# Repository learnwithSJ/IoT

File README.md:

# Smart AI Plug

An ESP32-S3 based IoT smart plug designed for remote and scheduled control of electrical appliances.

> **Project Status:** PCB Design Completed — Hardware Assembly and Testing Not Yet Performed.

## Overview

Smart AI Plug is a smart plug concept designed around the ESP32-S3 microcontroller. The system is intended to provide wireless appliance control along with scheduled operation.

The complete circuit and PCB were designed using **KiCad**.

## Features

* ESP32-S3 based design
* Single-channel relay control (SPDT)
* Wi-Fi and Bluetooth connectivity
* Relay-based appliance switching
* RTC-based scheduled operation
* USB-C interface
* Onboard RTC with battery backup (DS3231M + CH291-1220LF)
* Status LEDs - Network, Error, General indication
* Buzzer feedback (MLT-8530)
* 4x tactile switches for local control
* AC-DC power supply section
* PCB protection circuitry
* Compact PCB design

## 🏗️ System Architecture

```
220V AC Input
     │
     ▼
[F1 Fuse 500mA] ──→ [MOV RV1 Surge Protection]
     │
     ▼
[HLK-5M05] ──→ 5V DC
     │
     ├──→ [Relay K1 SPDT] ──→ Load Output (Screw Terminal J2)
     │
     └──→ [AMS1117-3.3] ──→ 3.3V DC
               │
               ├──→ [ESP32-S3-WROOM-1] ←→ WiFi / BLE
               ├──→ [DS3231M RTC] (I2C)
               ├──→ [Status LEDs]
               ├──→ [Buzzer MLT-8530]
               ├──→ [Tactile Switches x4]
               └──→ [USB-C] ──→ Firmware Flash / Serial Debug
```

---

## 🔧 Hardware Specifications

| Parameter | Details |
|---|---|
| Microcontroller | ESP32-S3-WROOM-1 |
| Input Voltage | 220V AC |
| Operating Voltage | 5V DC / 3.3V DC |
| Power Supply Module | HLK-5M05 (220VAC → 5VDC) |
| LDO Regulator | AMS1117-3.3 |
| Relay | SPDT — 1 Channel |
| RTC | DS3231M (I2C) |
| RTC Battery | CH291-1220LF (Coin Cell) |
| USB Connector | USB-C (USB 2.0) |
| ESD Protection | USBLC6-2P6 |
| Surge Protection | MOV 10D561K |
| Fuse | 500mA / 250V |
| Status LEDs | Red, Blue, Green |
| Buzzer | MLT-8530 |
| Switches | 4x Tactile + 1x Boot + 1x Reset |
| PCB Tool | KiCad 9.0.1 |
| Board Revision | Rev-v0.1.0A |

---

## PCB Design

The schematic and PCB layout were designed using **KiCad**.

## Repository Structure

```text
KiCad/          → KiCad schematic, PCB and project files
Documentation/  → Design documents and diagrams
Images/         → Project images
BOM/            → Bill of Materials
Firmware/       → Firmware documentation
```

## Project Status

The schematic and PCB layout have been completed in KiCad.

The current version is a **design/prototype-stage project**. Physical PCB fabrication, assembly, firmware deployment, and hardware testing have not yet been completed.

## Future Improvements

* Fabricate and assemble the PCB
* Develop and test ESP32-S3 firmware
* Add cloud-based appliance control
* Integrate voice assistant support
* Perform electrical safety and functional testing
* Optimize PCB size and power consumption

## 🏭 Manufacturing

Fabrication files are located in `Hardware/3-Manufacturing-Files/` and include:

- **Gerber files** - for PCB fabrication
- **BOM (Bill of Materials)** - component list with values and part numbers
- **CPL (Component Placement List)** - for SMT assembly

## Designed By

**Shubhank**

## Acknowledgements

Special thanks to **Ampnics** for creating and sharing the original Zeen AI Plug project and providing the YouTube tutorial and open-source resources that helped me understand and recreate this project.

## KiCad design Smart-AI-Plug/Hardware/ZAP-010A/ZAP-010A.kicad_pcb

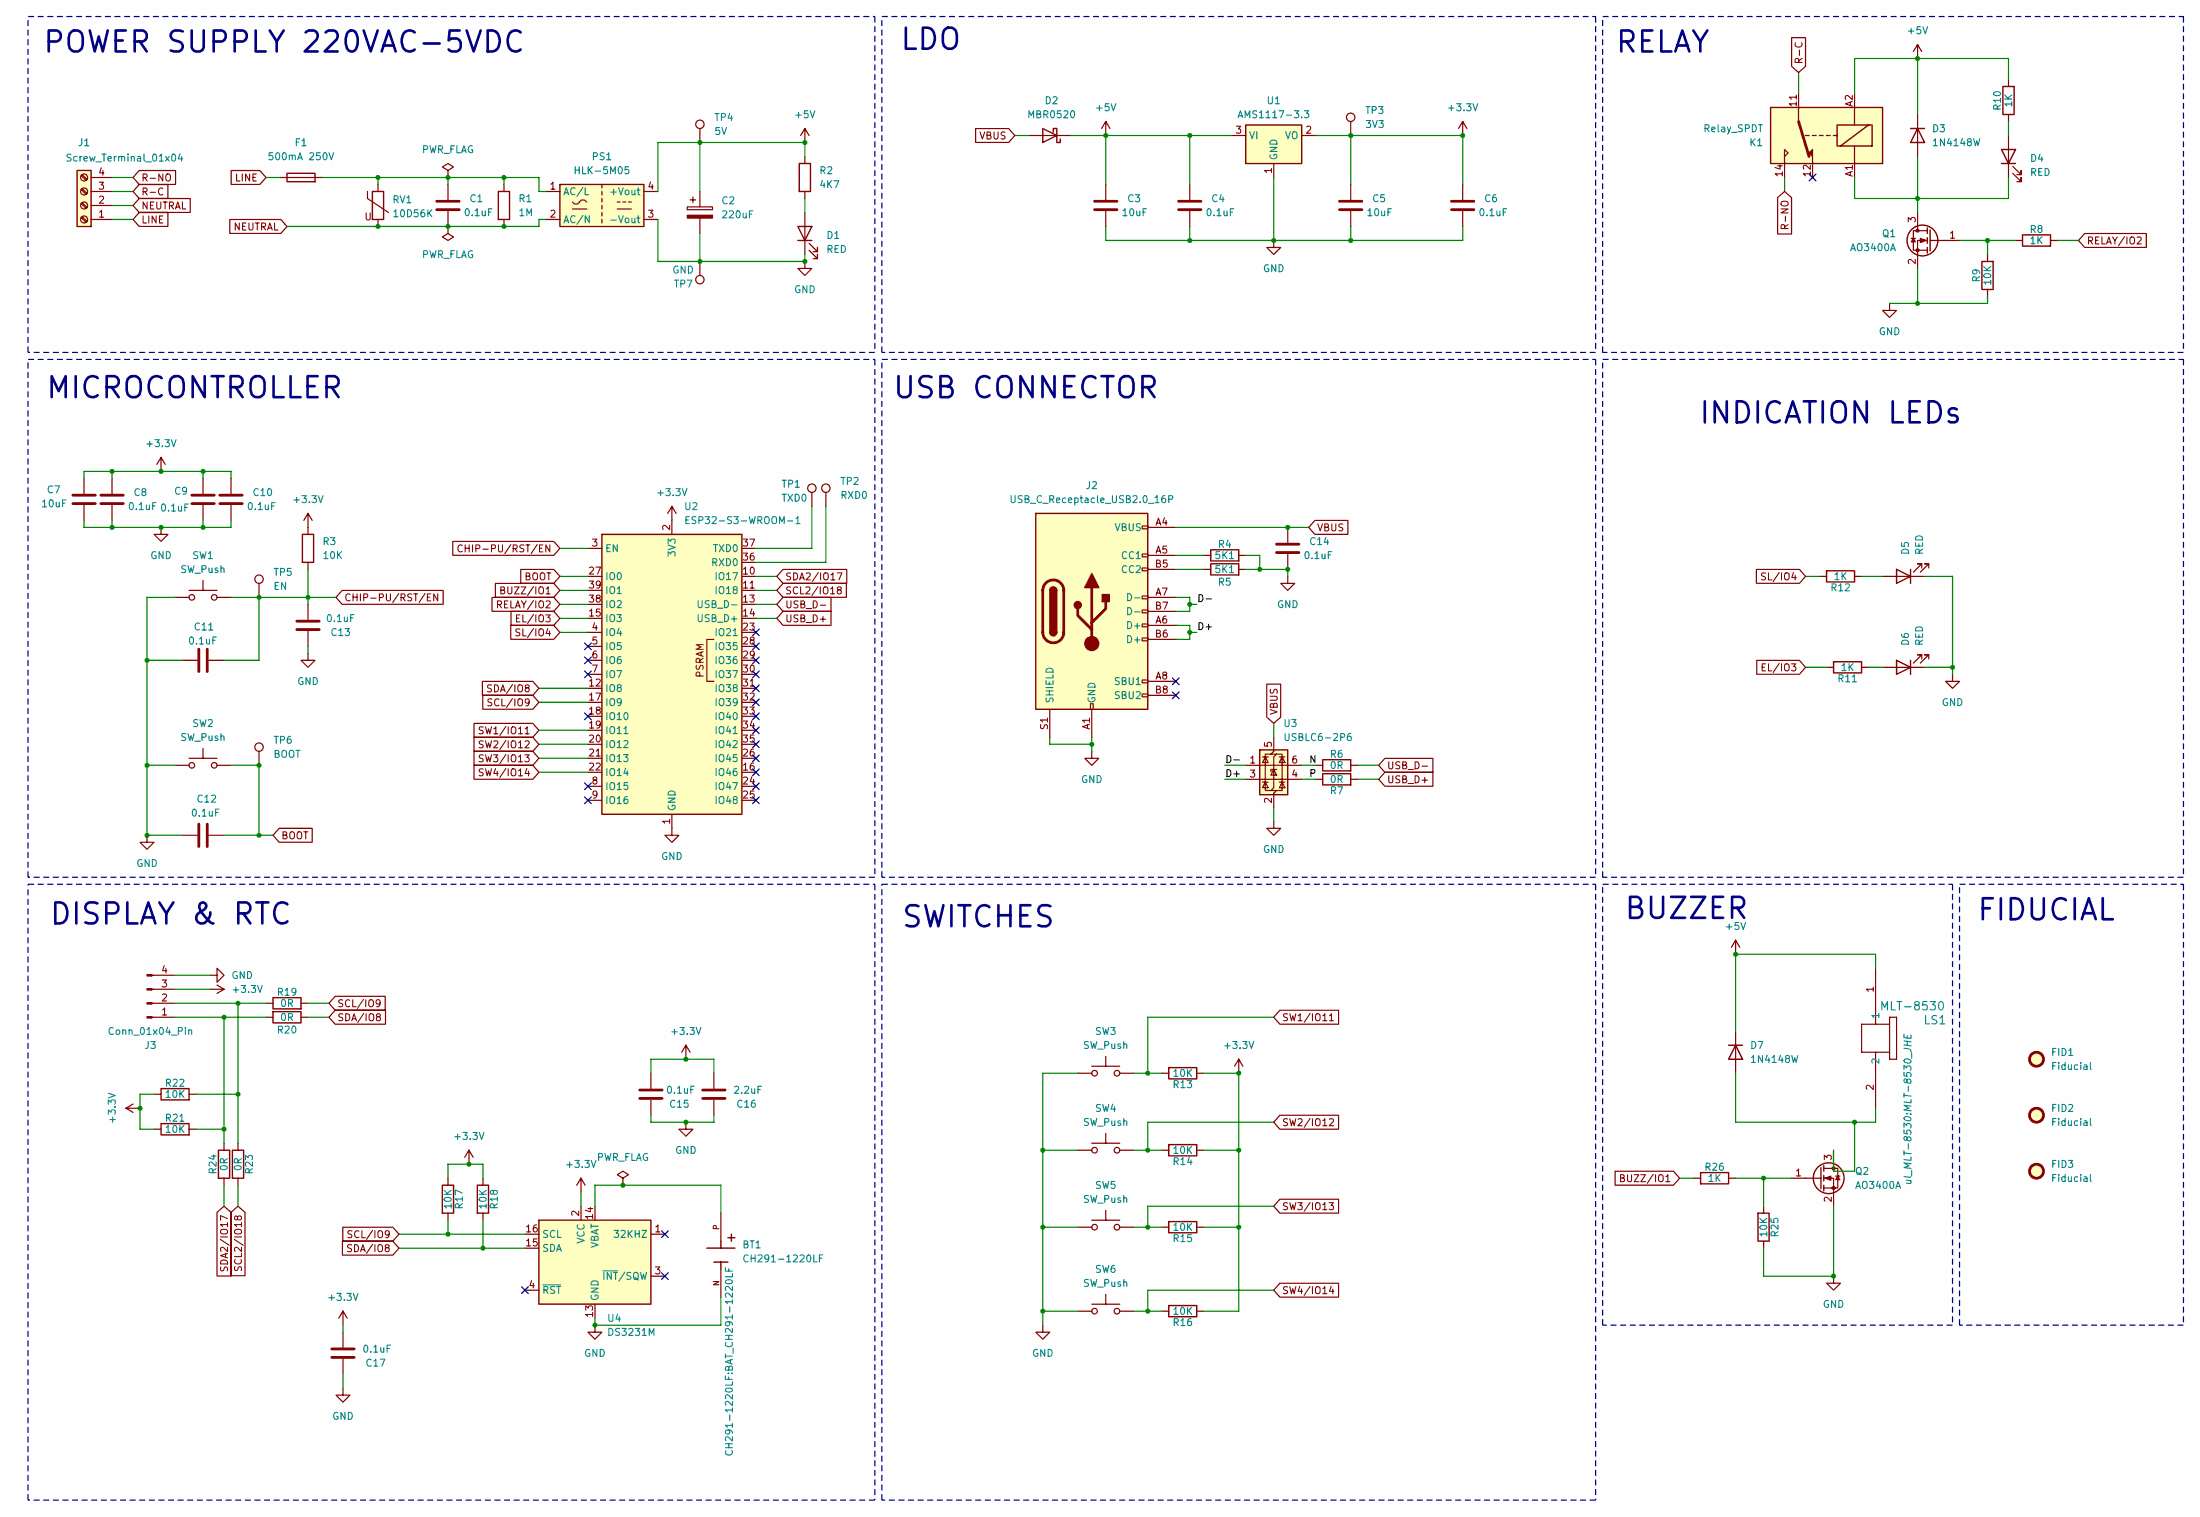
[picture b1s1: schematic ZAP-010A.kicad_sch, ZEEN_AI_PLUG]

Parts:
BT1: CH291-1220LF; BAT_CH291-1220LF; PARTREV A
C1: 0.1uF; C_Rect_L13.0mm_W6.0mm_P10.00mm_FKS3_FKP3_MKS4
C2: 220uF; CP_Elec_8x10
C3, C5, C7: 10uF; C_0805_2012Metric
C4, C6, C8, C9, C10, C11, C12, C13, C14, C15: 0.1uF; C_0603_1608Metric
C16: 2.2uF; C_0805_2012Metric
C17: 0.1uF; C_0805_2012Metric
D1, D5, D6: RED; LED_D3.0mm
D2: MBR0520; D_SOD-123
D3, D7: 1N4148W; D_SOD-123
D4: RED; LED_0603_1608Metric
F1: 500mA 250V; Fuse_Littelfuse_395Series
FID1, FID2, FID3: Fiducial; Fiducial_0.75mm_Mask1.5mm
J1: Screw_Terminal_01x04; TerminalBlock_bornier-4_P5.08mm
J2: USB_C_Receptacle_USB2.0_16P; USB_C_Receptacle_HCTL_HC-TYPE-C-16P-01A
J3: Conn_01x04_Pin; PinHeader_1x04_P2.54mm_Vertical
K1: Relay_SPDT; Relay_SPDT_Hongfa_HF3F-L-xx-1ZL1T
LS1: MLT-8530; MLT-8530_JHE
PS1: HLK-5M05; Converter_ACDC_Hi-Link_HLK-5Mxx
Q1, Q2: AO3400A; SOT-23
R1: 1M; R_Axial_DIN0207_L6.3mm_D2.5mm_P7.62mm_Horizontal
R2: 4K7; R_0603_1608Metric
R3, R9, R13, R14, R15, R16, R17, R18, R21, R22, R25: 10K; R_0603_1608Metric
R4, R5: 5K1; R_0603_1608Metric
R6, R7, R19, R20, R23, R24: 0R; R_0603_1608Metric
R8, R10, R11, R12, R26: 1K; R_0603_1608Metric
RV1: 10D56K; RV_Disc_D12mm_W5.8mm_P7.5mm
SW1, SW3, SW4, SW5, SW6: SW_Push; SW_PUSH_6mm
SW2: SW_Push; SW_Push_SPST_NO_Alps_SKRK
TP1: TXD0; TestPoint_Pad_D1.5mm
TP2: RXD0; TestPoint_Pad_D1.5mm
TP3: 3V3; TestPoint_Pad_D1.5mm
TP4: 5V; TestPoint_Pad_D1.5mm
TP5: EN; TestPoint_Pad_D1.5mm
TP6: BOOT; TestPoint_Pad_D1.5mm
TP7: GND; TestPoint_Pad_D1.5mm
U1: AMS1117-3.3; SOT-223-3_TabPin2
U2: ESP32-S3-WROOM-1
U3: USBLC6-2P6; SOT-666
U4: DS3231M; SOIC-16W_7.5x10.3mm_P1.27mm

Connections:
+3.3V: C5.1, C6.1, C7.1, C8.1, C9.1, C10.1, C15.1, C16.1, C17.1, J3.3, R3.1, R13.1, R14.1, R15.1, R16.1, R17.1, R18.1, R21.1, R22.1, TP3.1, U1.2 (VO), U2.2 (3V3), U4.2 (VCC)
+5V: C2.1, C3.1, C4.1, D2.1 (K), D3.1 (K), D7.1 (K), K1.A2, LS1.1, PS1.4 (+Vout), R2.1, R10.2, TP4.1, U1.3 (VI)
/D+: J2.A6 (D+), J2.B6 (D+), U3.3 (I/O2)
/D-: J2.A7 (D-), J2.B7 (D-), U3.1 (I/O1)
/N: R6.1, U3.6 (I/O1)
/P: R7.1, U3.4 (I/O2)
BOOT: C12.1, SW2.2, TP6.1, U2.27 (IO0)
BUZZ/IO1: R26.2, U2.39 (IO1)
CHIP-PU/RST/EN: C11.1, C13.2, R3.2, SW1.2, TP5.1, U2.3 (EN)
EL/IO3: R11.2, U2.15 (IO3)
GND: BT1.N, C2.2, C3.2, C4.2, C5.2, C6.2, C7.2, C8.2, C9.2, C10.2, C11.2, C12.2, C13.1, C14.2, C15.2, C16.2, C17.2, D1.1 (K), D5.1 (K), D6.1 (K), J2.A1 (GND), J2.A12 (GND), J2.B1 (GND), J2.B12 (GND), J2.S1 (SHIELD), J3.4, PS1.3 (-Vout), Q1.2 (S), Q2.2 (S), R4.2, R5.2, R9.1, R25.1, SW1.1, SW2.1, SW3.1, SW4.1, SW5.1, SW6.1, TP7.1, U1.1 (GND), U2.1 (GND), U2.40 (GND), U2.41 (GND), U3.2 (GND), U4.5 (GND), U4.6 (GND), U4.7 (GND), U4.8 (GND), U4.9 (GND), U4.10 (GND), U4.11 (GND), U4.12 (GND), U4.13 (GND)
LINE: F1.1, J1.1
NEUTRAL: C1.2, J1.2, PS1.2 (AC/N), R1.2, RV1.2
unnamed: D1.2 (A), R2.2
unnamed: D3.2 (A), D4.1 (K), K1.A1, Q1.3 (D)
unnamed: D4.2 (A), R10.1
unnamed: D5.2 (A), R12.1
unnamed: D6.2 (A), R11.1
unnamed: D7.2 (A), LS1.2, Q2.3 (D)
unnamed: J2.A5 (CC1), R4.1
unnamed: J2.B5 (CC2), R5.1
unnamed: J3.1, R20.2, R21.2, R24.1
unnamed: J3.2, R19.1, R22.2, R23.1
unnamed: C1.1, F1.2, PS1.1 (AC/L), R1.1, RV1.1
unnamed: Q1.1 (G), R8.1, R9.2
unnamed: Q2.1 (G), R25.2, R26.1
unnamed: TP2.1, U2.36 (RXD0)
unnamed: TP1.1, U2.37 (TXD0)
unnamed: BT1.P, U4.14 (VBAT)
R-C: J1.3, K1.11
R-NO: J1.4, K1.14
RELAY/IO2: R8.2, U2.38 (IO2)
SCL2/IO18: R23.2, U2.11 (IO18)
SCL/IO9: R17.2, R19.2, U2.17 (IO9), U4.16 (SCL)
SDA2/IO17: R24.2, U2.10 (IO17)
SDA/IO8: R18.2, R20.1, U2.12 (IO8), U4.15 (SDA)
SL/IO4: R12.2, U2.4 (IO4)
SW1/IO11: R13.2, SW3.2, U2.19 (IO11)
SW2/IO12: R14.2, SW4.2, U2.20 (IO12)
SW3/IO13: R15.2, SW5.2, U2.21 (IO13)
SW4/IO14: R16.2, SW6.2, U2.22 (IO14)
USB_D+: R7.2, U2.14 (USB_D+)
USB_D-: R6.2, U2.13 (USB_D-)
VBUS: C14.1, D2.2 (A), J2.A4 (VBUS), J2.A9 (VBUS), J2.B4 (VBUS), J2.B9 (VBUS), U3.5 (VBUS)

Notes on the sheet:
DISPLAY & RTC
LDO
BUZZER
POWER SUPPLY 220VAC-5VDC
INDICATION LEDs
MICROCONTROLLER
RELAY
USB CONNECTOR
SWITCHES
FIDUCIAL

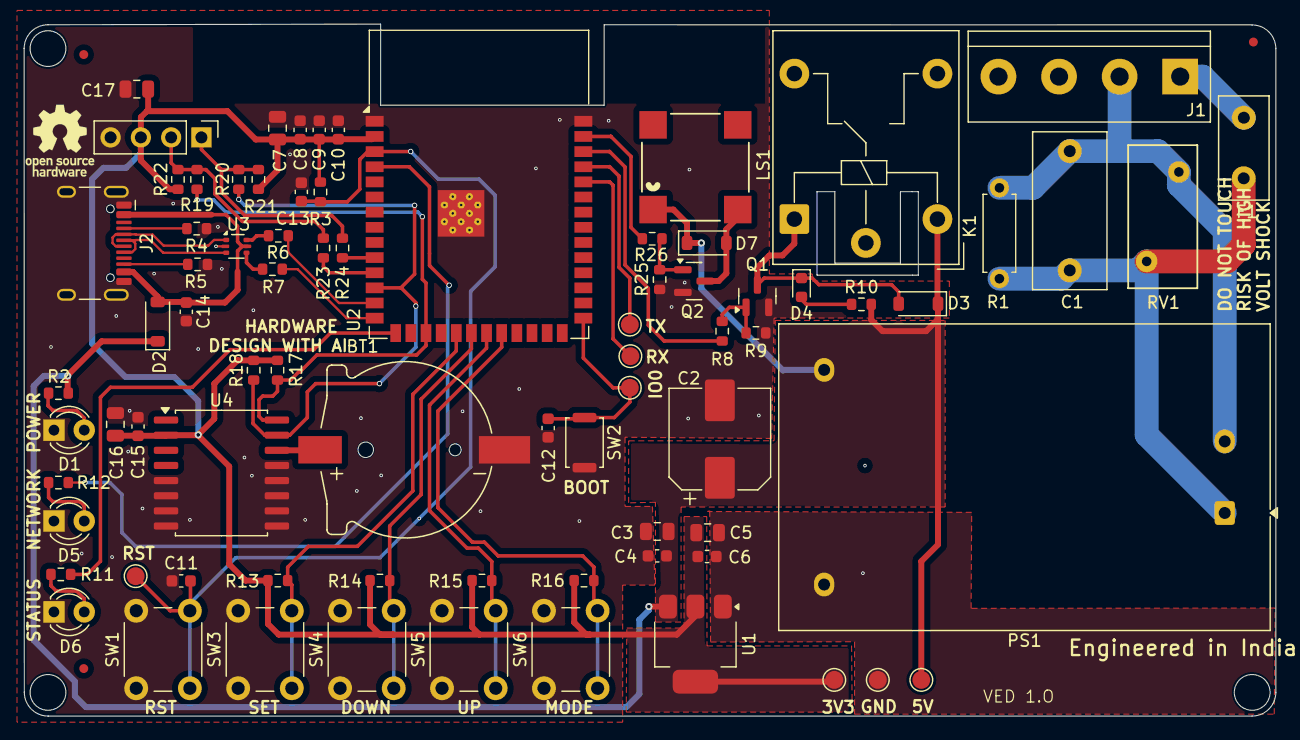
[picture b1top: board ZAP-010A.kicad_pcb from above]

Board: 2 copper layers, 105.0 x 58.0 mm, 81 parts (0 on the bottom side), 44 nets.
